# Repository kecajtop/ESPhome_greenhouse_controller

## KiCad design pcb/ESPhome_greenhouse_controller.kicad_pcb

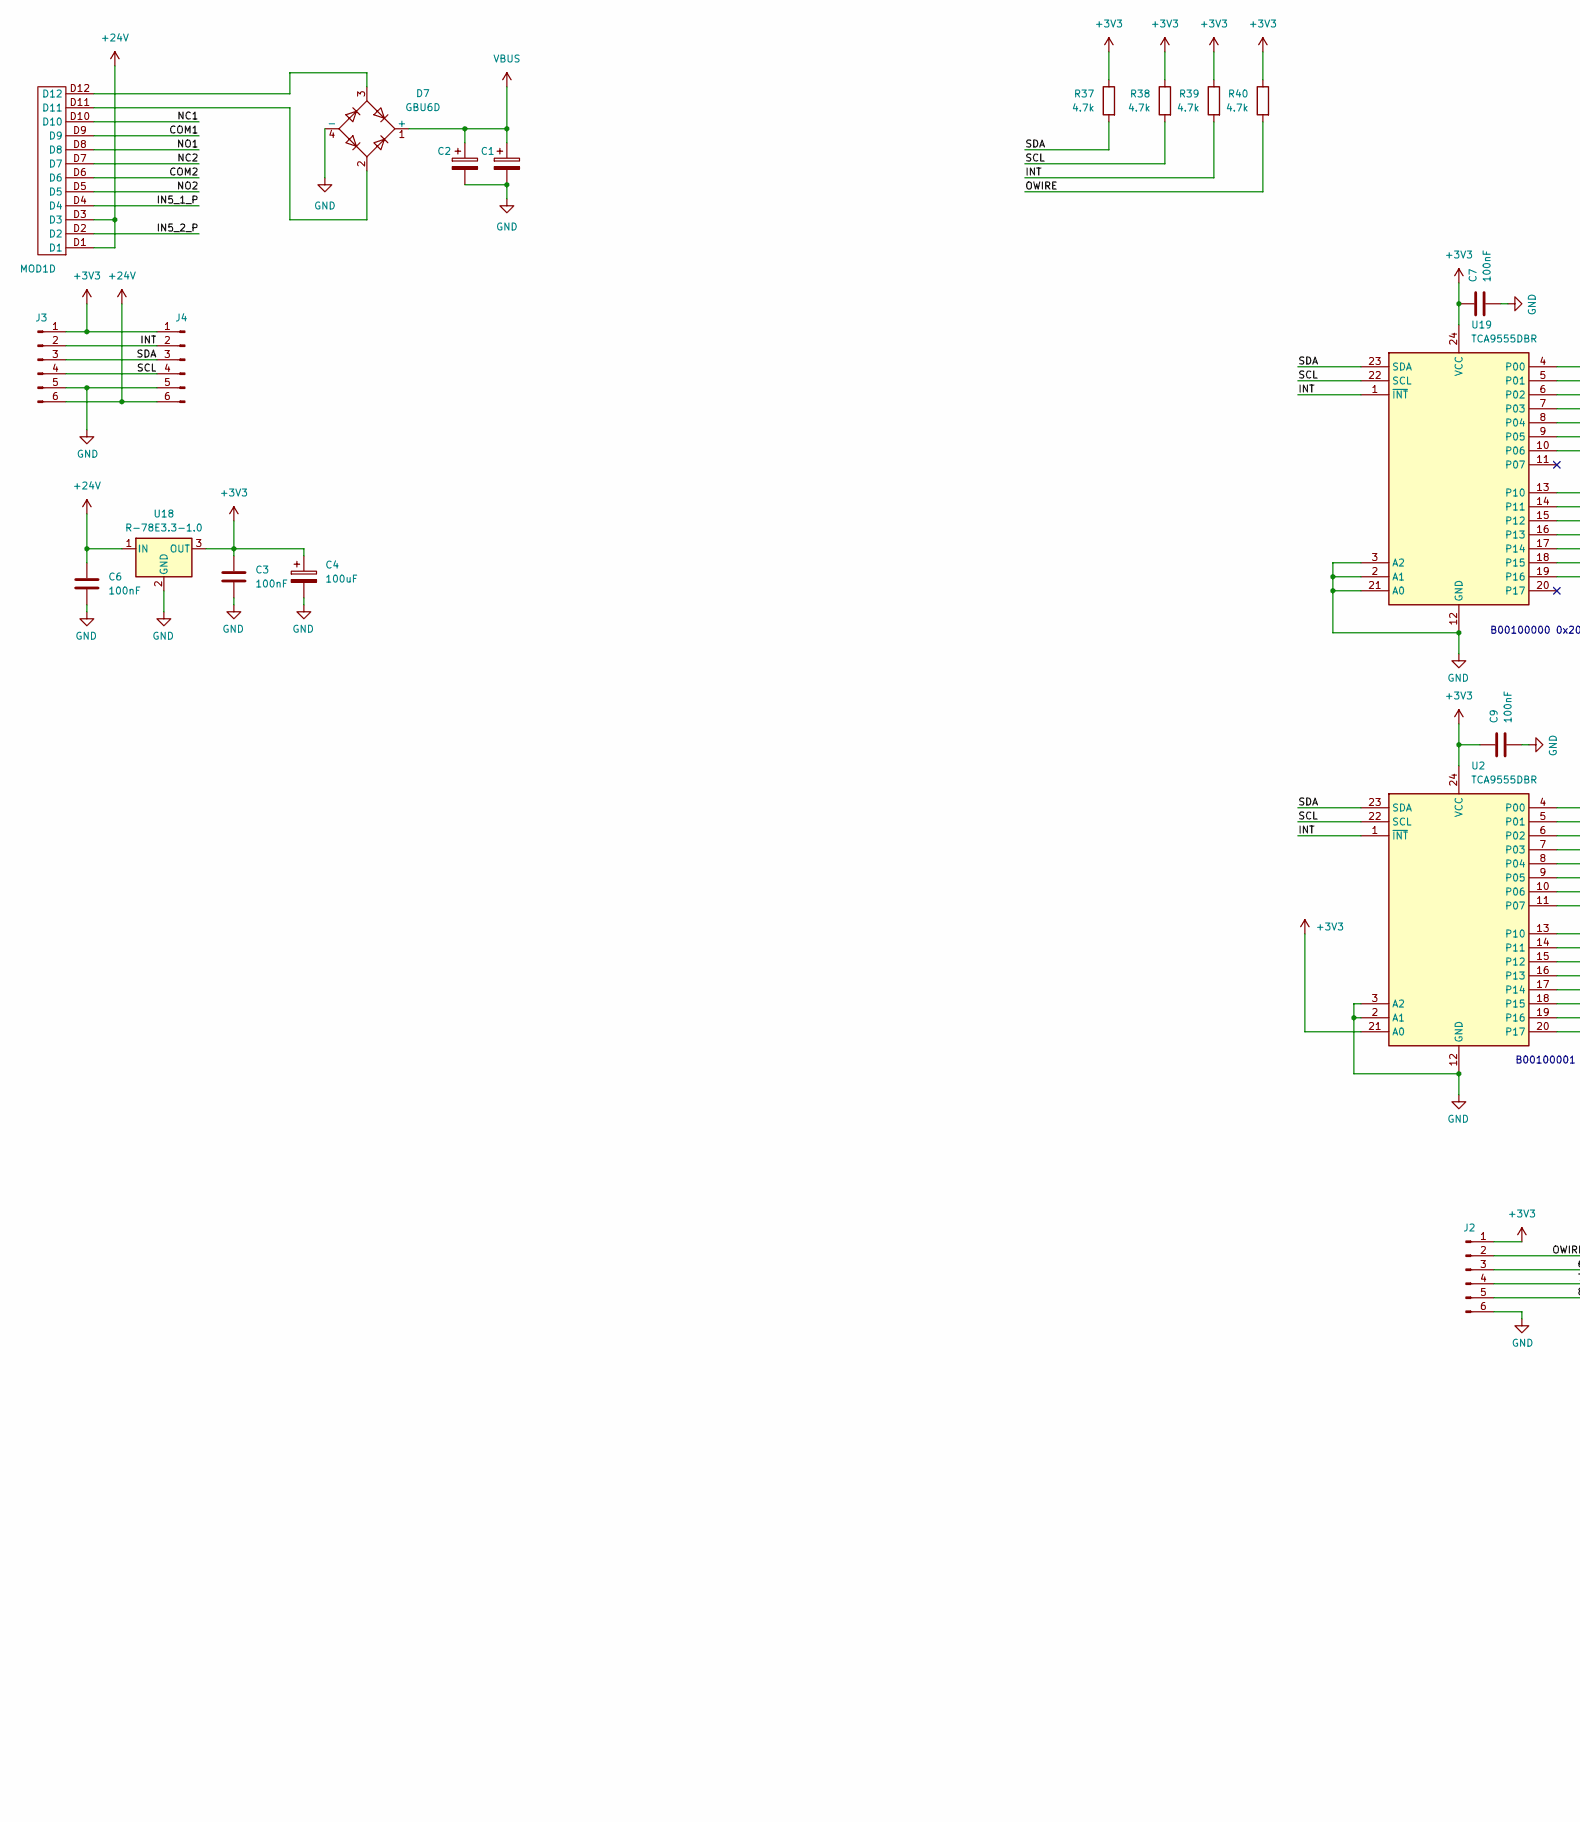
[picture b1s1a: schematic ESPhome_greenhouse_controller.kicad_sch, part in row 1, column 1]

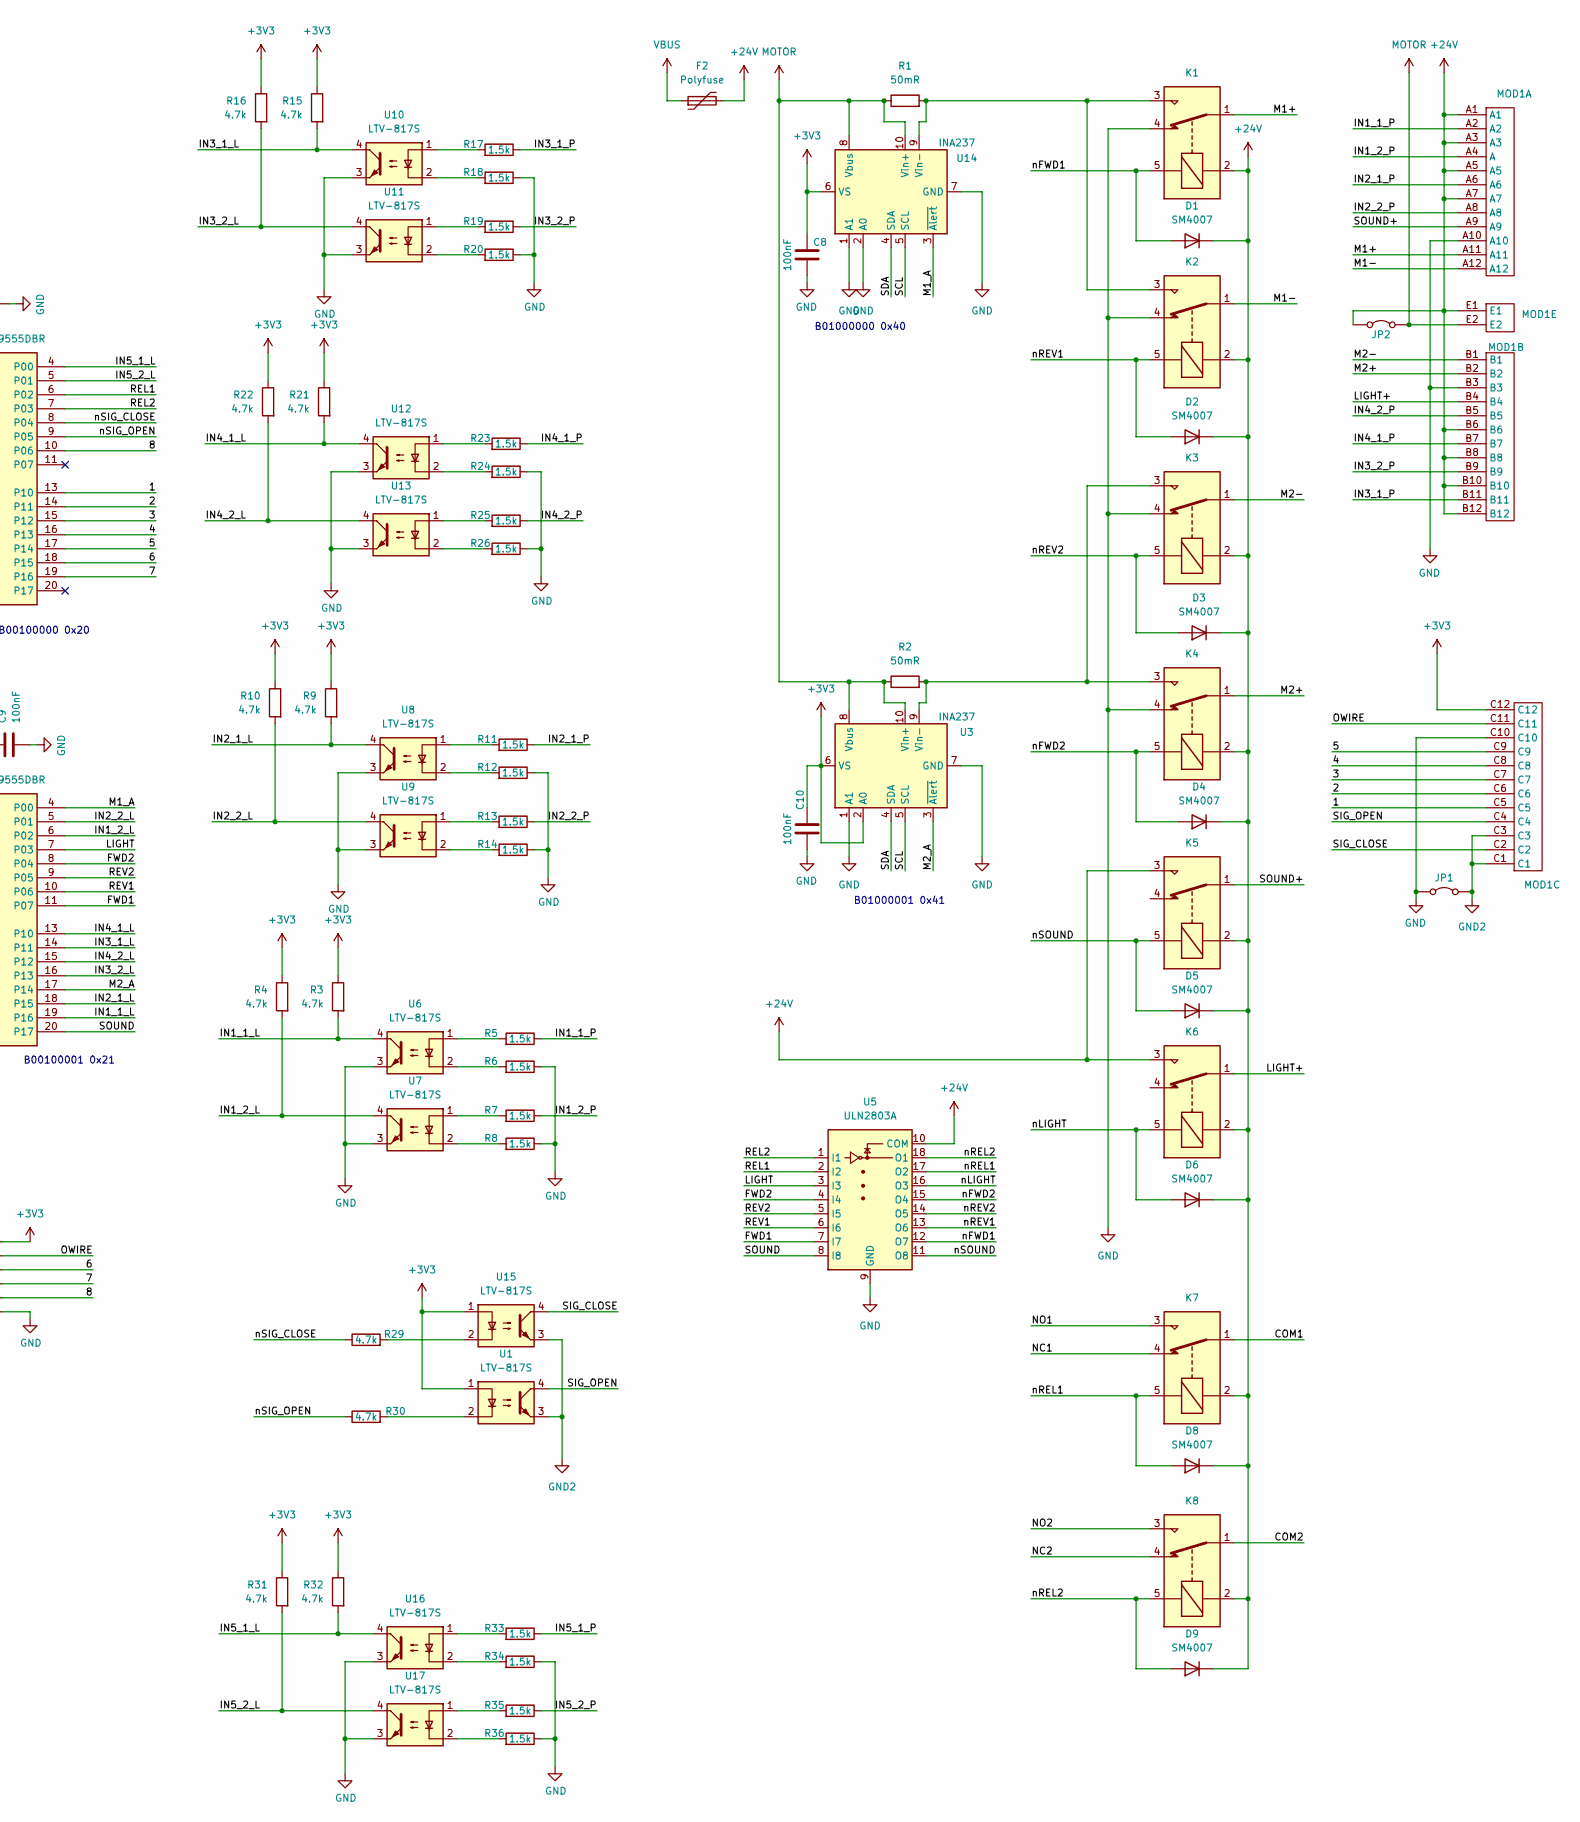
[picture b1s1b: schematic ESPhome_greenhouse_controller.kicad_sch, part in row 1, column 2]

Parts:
C1, C2: EKM227M1HG1BRRSHP; CP_Radial_D10.0mm_P5.00mm
C3, C6: 100nF; C_0805_2012Metric
C4: 100uF; CP_Radial_D8.0mm_P3.50mm
C7, C8, C9, C10: 100nF; C_0603_1608Metric
D1, D2, D3, D4, D5, D6, D8, D9: SM4007; D_MELF
D7: GBU6D; Diode_Bridge_Vishay_GBU
F2: Polyfuse; Fuse_Bourns_MF-RHT1100
J2, J3, J4: Conn_01x05_Pin; JST_EH_B6B-EH-A_1x06_P2.50mm_Vertical
JP1, JP2: Jumper_2_Bridged; SolderJumper-2_P1.3mm_Open_RoundedPad1.0x1.5mm
K1, K2, K3, K4, K5, K6, K7, K8: SANYOU_SRD_Form_C; Relay_SPDT_SANYOU_SRD_Series_Form_C
MOD1: ZD1008
R1, R2: 50mR; R_1206_3216Metric
R3, R4, R9, R10, R15, R16, R21, R22, R29, R30, R31, R32, R37, R38, R39, R40: R0603_4.7k_1%_100mW_100PPM_AC; R_0603_1608Metric; Manufacturer Part Number AC0603FR-074K7L; LCSC C23162
R5, R6, R7, R8, R11, R12, R13, R14, R17, R18, R19, R20, R23, R24, R25, R26, R33, R34, R35, R36: R0805_1.5k_1%_125mW_100PPM_AC; R_0805_2012Metric; Manufacturer Part Number AC0805FR-071K5L; LCSC C22843
U1, U6, U7, U8, U9, U10, U11, U12, U13, U15, U16, U17: LTV-817S; SMDIP-4_W9.53mm; LCSC C109225
U2, U19: TCA9555DBR; SSOP-24_5.3x8.2mm_P0.65mm
U3, U14: INA237; VSSOP-10_3x3mm_P0.5mm; LCSC C2864837
U5: ULN2803A; SOIC-18W_7.5x11.6mm_P1.27mm; LCSC C9683
U18: R-78E3.3-1.0; Converter_DCDC_RECOM_R-78E-0.5_THT

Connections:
+3V3: C3.1, C4.1, C7.1, C8.1, C9.1, C10.1, J2.1, J3.1, J4.1, MOD1.C12, R3.1, R4.1, R9.1, R10.1, R15.1, R16.1, R21.1, R22.1, R31.1, R32.1, R37.1, R38.1, R39.1, R40.1, U1.1, U2.21 (A0), U2.24 (VCC), U3.2 (A0), U3.6 (VS), U14.6 (VS), U15.1, U18.3 (OUT), U19.24 (VCC)
+24V: C6.1, D1.1 (K), D2.1 (K), D3.1 (K), D4.1 (K), D5.1 (K), D6.1 (K), D8.1 (K), D9.1 (K), F2.2, J3.6, J4.6, JP2.1 (A), K1.2, K2.2, K3.2, K4.2, K5.2, K5.3, K6.2, K6.3, K7.2, K8.2, MOD1.A1, MOD1.A3, MOD1.A5, MOD1.A7, MOD1.B6, MOD1.B8, MOD1.B10, MOD1.B12, MOD1.D1, MOD1.D3, MOD1.E1, U5.10 (COM), U18.1 (IN)
/1: MOD1.C5, U19.13 (P10)
/2: MOD1.C6, U19.14 (P11)
/3: MOD1.C7, U19.15 (P12)
/4: MOD1.C8, U19.16 (P13)
/5: MOD1.C9, U19.17 (P14)
/6: J2.3, U19.18 (P15)
/7: J2.4, U19.19 (P16)
/8: J2.5, U19.10 (P06)
/COM1: K7.1, MOD1.D9
/COM2: K8.1, MOD1.D6
/FWD1: U2.11 (P07), U5.7 (I7)
/FWD2: U2.8 (P04), U5.4 (I4)
/IN1_1_L: R3.2, U2.19 (P16), U6.4
/IN1_1_P: MOD1.A2, R5.1
/IN1_2_L: R4.2, U2.6 (P02), U7.4
/IN1_2_P: MOD1.A4 (A), R7.1
/IN2_1_L: R9.2, U2.18 (P15), U8.4
/IN2_1_P: MOD1.A6, R11.1
/IN2_2_L: R10.2, U2.5 (P01), U9.4
/IN2_2_P: MOD1.A8, R13.1
/IN3_1_L: R15.2, U2.14 (P11), U10.4
/IN3_1_P: MOD1.B11, R17.1
/IN3_2_L: R16.2, U2.16 (P13), U11.4
/IN3_2_P: MOD1.B9, R19.1
/IN4_1_L: R21.2, U2.13 (P10), U12.4
/IN4_1_P: MOD1.B7, R23.1
/IN4_2_L: R22.2, U2.15 (P12), U13.4
/IN4_2_P: MOD1.B5, R25.1
/IN5_1_L: R32.2, U16.4, U19.4 (P00)
/IN5_1_P: MOD1.D4, R33.1
/IN5_2_L: R31.2, U17.4, U19.5 (P01)
/IN5_2_P: MOD1.D2, R35.1
/INT: J3.2, J4.2, R39.2, U2.1 (~INT), U19.1 (~INT)
/LIGHT: U2.7 (P03), U5.3 (I3)
/LIGHT+: K6.1, MOD1.B4
/M1+: K1.1, MOD1.A11
/M1-: K2.1, MOD1.A12
/M1_A: U2.4 (P00), U14.3 (~Alert)
/M2+: K4.1, MOD1.B2
/M2-: K3.1, MOD1.B1
/M2_A: U2.17 (P14), U3.3 (~Alert)
/NC1: K7.4, MOD1.D10
/NC2: K8.4, MOD1.D7
/NO1: K7.3, MOD1.D8
/NO2: K8.3, MOD1.D5
/OWIRE: J2.2, MOD1.C11, R40.2
/REL1: U5.2 (I2), U19.6 (P02)
/REL2: U5.1 (I1), U19.7 (P03)
/REV1: U2.10 (P06), U5.6 (I6)
/REV2: U2.9 (P05), U5.5 (I5)
/SCL: J3.4, J4.4, R38.2, U2.22 (SCL), U3.5 (SCL), U14.5 (SCL), U19.22 (SCL)
/SDA: J3.3, J4.3, R37.2, U2.23 (SDA), U3.4 (SDA), U14.4 (SDA), U19.23 (SDA)
/SIG_CLOSE: MOD1.C2, U15.4
/SIG_OPEN: MOD1.C4, U1.4
/SOUND: U2.20 (P17), U5.8 (I8)
/SOUND+: K5.1, MOD1.A9
/nFWD1: D1.2 (A), K1.5, U5.12 (O7)
/nFWD2: D4.2 (A), K4.5, U5.15 (O4)
/nLIGHT: D6.2 (A), K6.5, U5.16 (O3)
/nREL1: D8.2 (A), K7.5, U5.17 (O2)
/nREL2: D9.2 (A), K8.5, U5.18 (O1)
/nREV1: D2.2 (A), K2.5, U5.13 (O6)
/nREV2: D3.2 (A), K3.5, U5.14 (O5)
/nSIG_CLOSE: R29.1, U19.8 (P04)
/nSIG_OPEN: R30.1, U19.9 (P05)
/nSOUND: D5.2 (A), K5.5, U5.11 (O8)
GND: C1.2, C2.2, C3.2, C4.2, C6.2, C7.2, C8.2, C9.2, C10.2, D7.4 (-), J2.6, J3.5, J4.5, JP1.1 (A), K1.4, K2.4, K3.4, K4.4, MOD1.A10, MOD1.B3, MOD1.C10, R6.1, R8.1, R12.1, R14.1, R18.1, R20.1, R24.1, R26.1, R34.1, R36.1, U2.2 (A1), U2.3 (A2), U2.12 (GND), U3.1 (A1), U3.7 (GND), U5.9 (GND), U6.3, U7.3, U8.3, U9.3, U10.3, U11.3, U12.3, U13.3, U14.1 (A1), U14.2 (A0), U14.7 (GND), U16.3, U17.3, U18.2 (GND), U19.2 (A1), U19.3 (A2), U19.12 (GND), U19.21 (A0)
GND2: JP1.2 (B), MOD1.C1, MOD1.C3, U1.3, U15.3
MOTOR: JP2.2 (B), MOD1.E2, R1.1, R2.1, U3.8 (Vbus), U3.10 (Vin+), U14.8 (Vbus), U14.10 (Vin+)
unnamed: D7.2, MOD1.D11
unnamed: D7.3, MOD1.D12
unnamed: R5.2, U6.1
unnamed: R6.2, U6.2
unnamed: R7.2, U7.1
unnamed: R8.2, U7.2
unnamed: R11.2, U8.1
unnamed: R12.2, U8.2
unnamed: R13.2, U9.1
unnamed: R14.2, U9.2
unnamed: R17.2, U10.1
unnamed: R18.2, U10.2
unnamed: R19.2, U11.1
unnamed: R20.2, U11.2
unnamed: R23.2, U12.1
unnamed: R24.2, U12.2
unnamed: R25.2, U13.1
unnamed: R26.2, U13.2
unnamed: R29.2, U15.2
unnamed: R30.2, U1.2
unnamed: R33.2, U16.1
unnamed: R34.2, U16.2
unnamed: R35.2, U17.1
unnamed: R36.2, U17.2
unnamed: K3.3, K4.3, R2.2, U3.9 (Vin-)
unnamed: K1.3, K2.3, R1.2, U14.9 (Vin-)
VBUS: C1.1, C2.1, D7.1 (+), F2.1

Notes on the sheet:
B01000000 0x40
B00100000 0x20
B00100001 0x21
B01000001 0x41

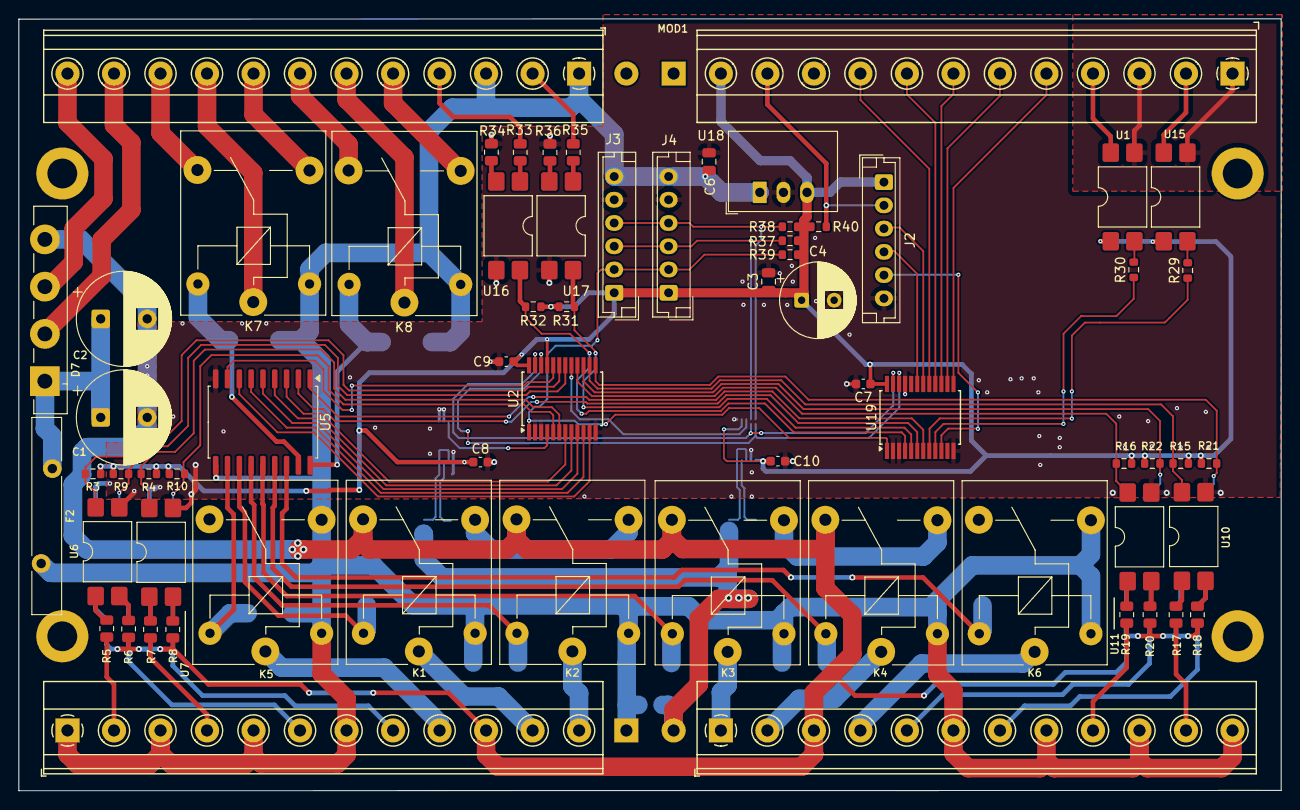
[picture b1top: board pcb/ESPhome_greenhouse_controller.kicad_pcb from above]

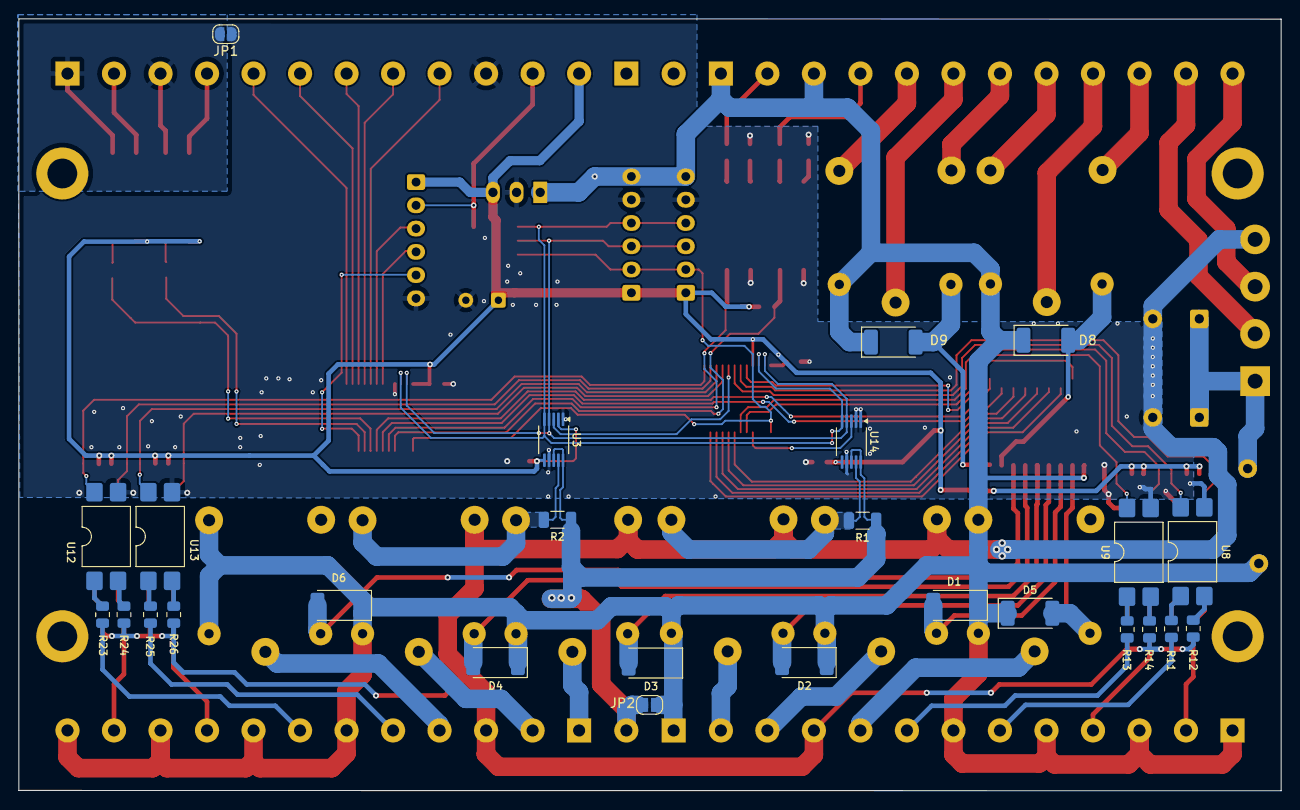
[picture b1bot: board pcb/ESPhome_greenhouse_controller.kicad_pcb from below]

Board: 2 copper layers, 135.7 x 83.0 mm, 89 parts (26 on the bottom side), 98 nets.

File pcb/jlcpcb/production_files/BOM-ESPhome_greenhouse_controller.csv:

Comment,Designator,Footprint,LCSC,Quantity
LTV-817S,"U1,U10,U11,U12,U13,U15,U16,U17,U6,U7,U8,U9",SMDIP-4_W9.53mm,C109225,12
R0805_1.5k_1%_125mW_100PPM_AC,"R11,R12,R13,R14,R17,R18,R19,R20,R23,R24,R25,R26,R33,R34,R35,R36,R5,R6,R7,R8",R_0805_2012Metric,C22843,20
R0603_4.7k_1%_100mW_100PPM_AC,"R10,R15,R16,R21,R22,R27,R28,R29,R3,R30,R31,R32,R37,R38,R39,R4,R40,R9",R_0603_1608Metric,C23162,18
INA237,"U14,U3",VSSOP-10_3x3mm_P0.5mm,C2864837,2
MCP23017_SO,"U2,U4",SOIC-28W_7.5x17.9mm_P1.27mm,C47023,2
ULN2803A,U5,SOIC-18W_7.5x11.6mm_P1.27mm,C9683,1
100nF,C6,C_0805_2012Metric,,1
100nF,C3,C_0805_2012Metric,,1
100nF,C8,C_0603_1608Metric,,1
100nF,C7,C_0603_1608Metric,,1
100nF,C9,C_0603_1608Metric,,1
100nF,C10,C_0603_1608Metric,,1
SM4007,D8,D_MELF,,1
SM4007,D9,D_MELF,,1
SM4007,D2,D_MELF,,1
SM4007,D6,D_MELF,,1
SM4007,D4,D_MELF,,1
SM4007,D1,D_MELF,,1
SM4007,D5,D_MELF,,1
50mR,R2,R_1206_3216Metric,,1
50mR,R1,R_1206_3216Metric,,1
SM4007,D3,D_MELF,,1

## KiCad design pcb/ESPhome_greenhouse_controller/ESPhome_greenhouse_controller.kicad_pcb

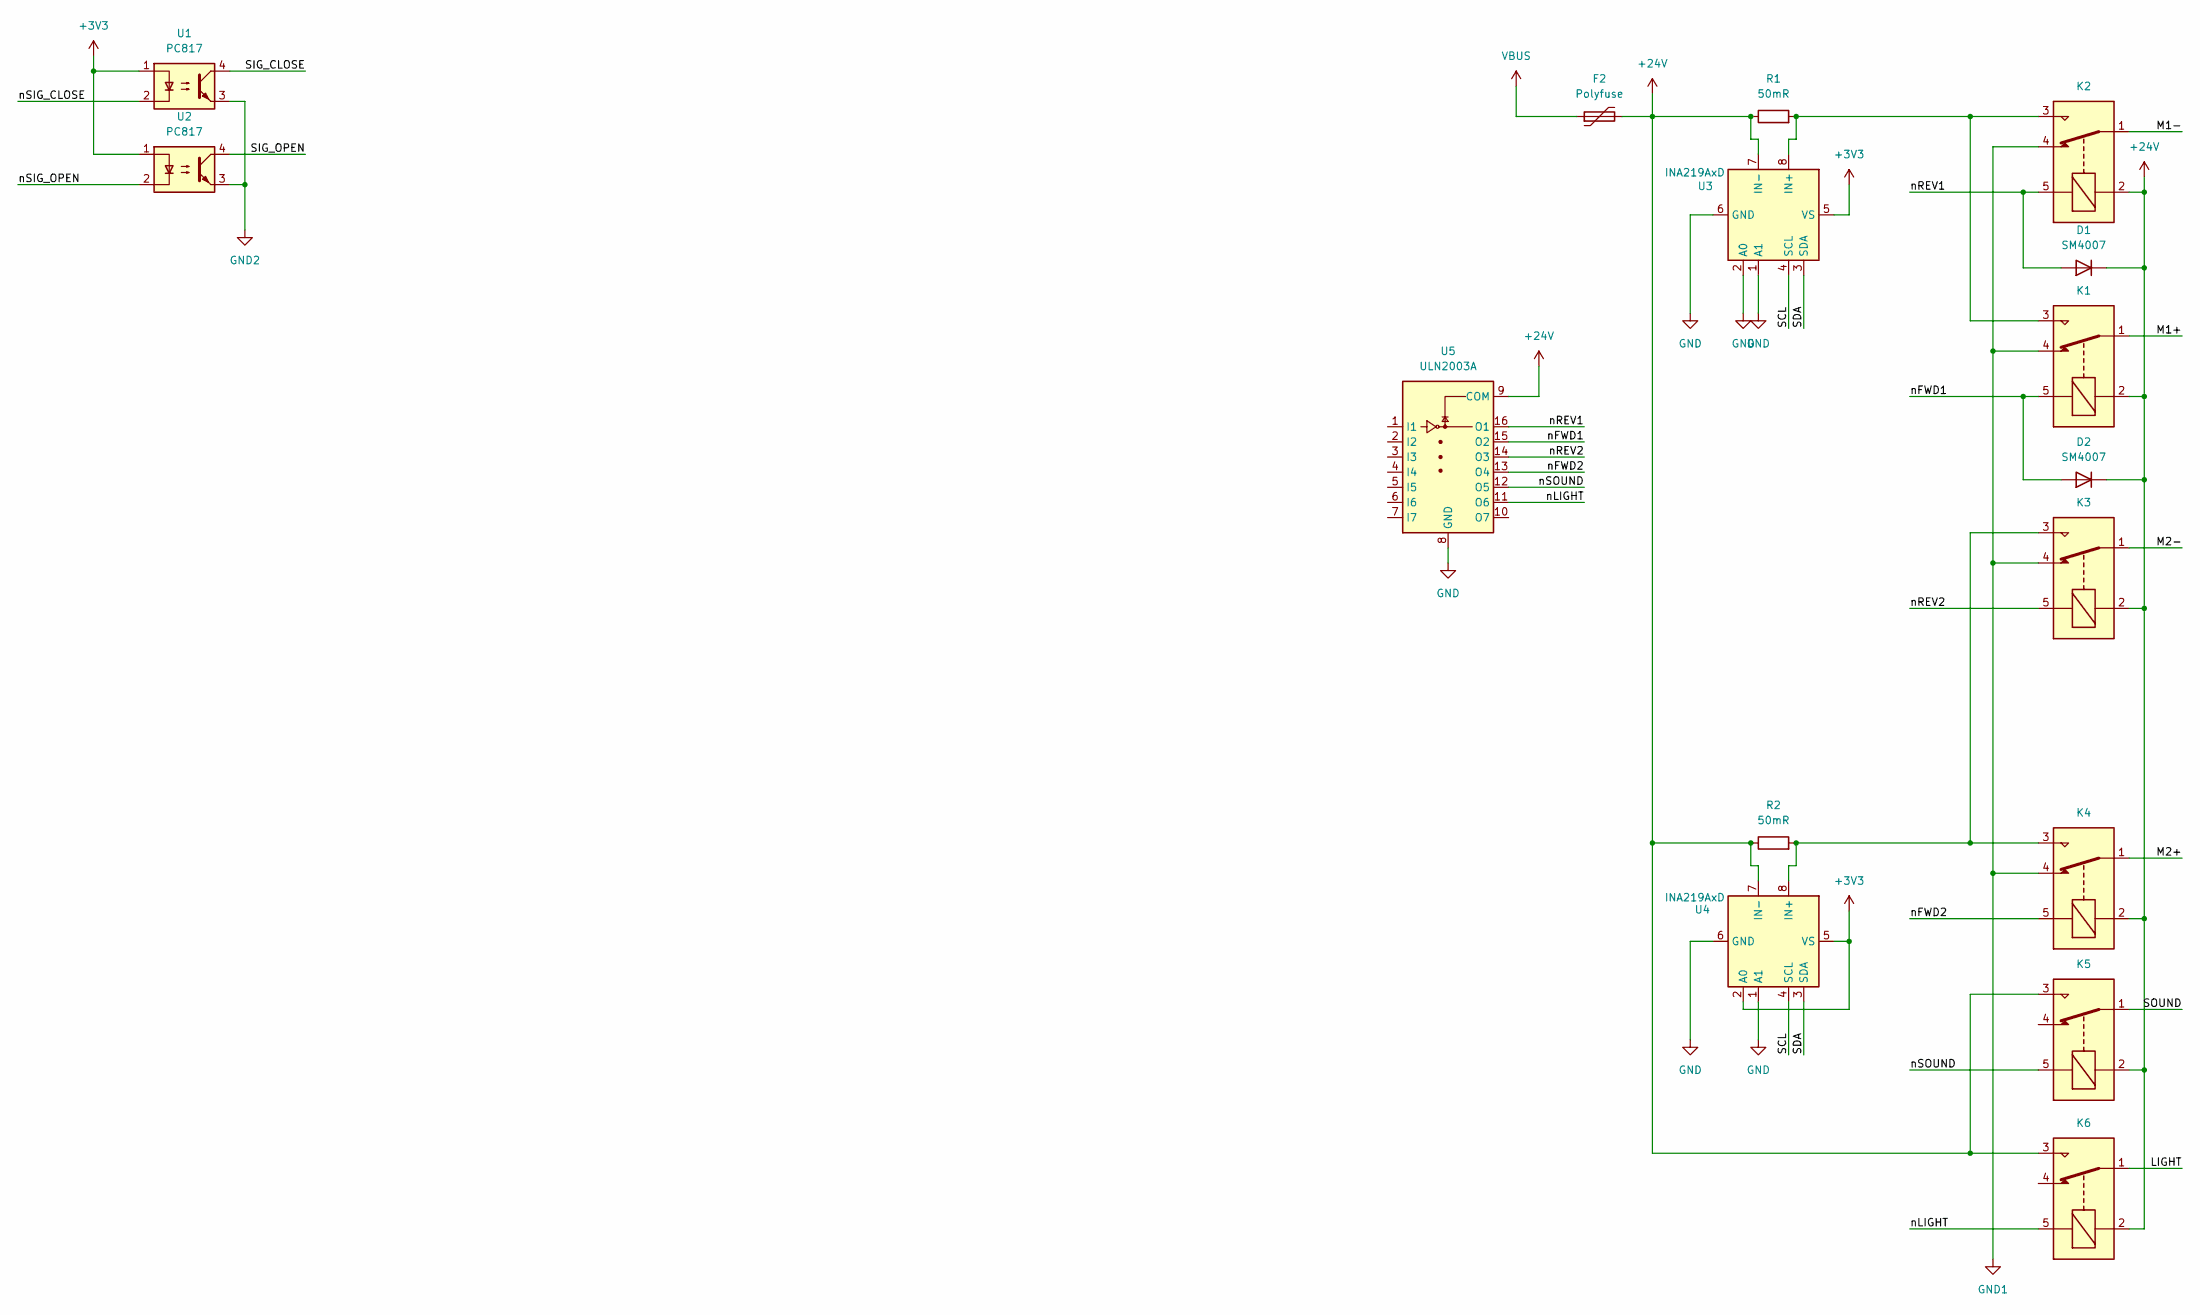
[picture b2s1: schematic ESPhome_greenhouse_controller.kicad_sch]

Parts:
D1, D2: SM4007; D_MELF
F2: Polyfuse; Fuse_Bourns_MF-RHT1100
K1, K2, K3, K4, K5, K6: SANYOU_SRD_Form_C; Relay_SPDT_SANYOU_SRD_Series_Form_C
R1, R2: 50mR; R_1206_3216Metric
U1, U2: PC817; DIP-4_W7.62mm
U3, U4: INA219AxD; SOIC-8_3.9x4.9mm_P1.27mm
U5: ULN2003A

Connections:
+3V3: U1.1, U2.1, U3.5 (VS), U4.2 (A0), U4.5 (VS)
+24V: D1.1 (K), D2.1 (K), F2.2, K1.2, K2.2, K3.2, K4.2, K5.2, K5.3, K6.2, K6.3, R1.1, R2.1, U3.7 (IN-), U4.7 (IN-), U5.9 (COM)
/LIGHT: K6.1
/M1+: K1.1
/M1-: K2.1
/M2+: K4.1
/M2-: K3.1
/SCL: U3.4 (SCL), U4.4 (SCL)
/SDA: U3.3 (SDA), U4.3 (SDA)
/SIG_CLOSE: U1.4
/SIG_OPEN: U2.4
/SOUND: K5.1
/nFWD1: D2.2 (A), K1.5, U5.15 (O2)
/nFWD2: K4.5, U5.13 (O4)
/nLIGHT: K6.5, U5.11 (O6)
/nREV1: D1.2 (A), K2.5, U5.16 (O1)
/nREV2: K3.5, U5.14 (O3)
/nSIG_CLOSE: U1.2
/nSIG_OPEN: U2.2
/nSOUND: K5.5, U5.12 (O5)
GND: U3.1 (A1), U3.2 (A0), U3.6 (GND), U4.1 (A1), U4.6 (GND), U5.8 (GND)
GND1: K1.4, K2.4, K3.4, K4.4
GND2: U1.3, U2.3
unnamed: K1.3, K2.3, R1.2, U3.8 (IN+)
unnamed: K3.3, K4.3, R2.2, U4.8 (IN+)
VBUS: F2.1

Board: 2 copper layers, 15 parts (0 on the bottom side), 11 nets, no tracks yet.
